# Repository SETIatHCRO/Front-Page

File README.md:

# ata_docs
Documentation related to the Allen Telescope Array at the Hat Creek Radio Observatory in Hat Creek, California

Contents:

[**Analog-Signal-Components:**](Analog-Signal-Components) Documents relating to analog signal components

*Librarian: Alexander Pollak*

[**Antenna:**](Antenna) Documents relating to Antenna geometry and optical design

*Librarian: Alexander Pollak*

[**Antonio-Feed:**](Antonio-Feed) Documents related to V2 Antonio Feeds

*Librarian: Alexander Pollak*

[**Beamformer:**](Beamformer) Documents related to the first ATA beamformer

*Librarian: Billy Barott*

[**EMI:**](EMI) Documents related to site and device electromagnetic interference (EMI/RFI)

*Librarian: Janusz Kulpa*

[**HCRO-Network-Infrastructure:**](HCRO-Network-Infrastructure) Documents and drawings related to the HCRO ethernet infrastructure 

*Librarian: Alexander Pollak*

[**HCRO-Time-Standard:**](HCRO-Time-Standard) Documents and drawings related to the 1pps and 10MHz time distribution.

*Librarian: Alexander Pollak*

[**HVAC-Signal-Processing-Room:**](HVAC-Signal-Processing-Room) Documents and drawings related to the HVAC upgrade.

*Librarian: Alexander Pollak*

[**SITE:**](SITE) Documents related to the HCRO Site

*Librarian: Jon Richards*

[**SonATA:**](SonATA) Documents related to the SETI on ATA (SonATA) System

*Librarian: Jon Richards*

[**NOTES:**](NOTES) The NOTES stored on tumulus. General operating procedures.

*Librarian: Jon Richards*

[**Network:**](Network) Documents and drawings related to network and computer access..

*Librarian: Jon Richards*

Go to the [-> head over to wiki](https://github.com/SETIatHCRO/ata_docs/wiki)

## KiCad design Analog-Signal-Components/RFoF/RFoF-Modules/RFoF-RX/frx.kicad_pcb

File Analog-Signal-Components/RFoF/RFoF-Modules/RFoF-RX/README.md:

# DSA2000 Fiber Receiver

This repository contains the hardware design for the RF over fiber receiver module.
This module provides the data center-local analog signal processing following the conversion of optical to RF with a photodiode.
It is designed to interface with the "Radio Camera Frontend" card, and hence uses board-to-board connectors for the digital control and RF output.
Additionally, this module provides several monitor and control points that will eventually be integrated into the telescope's global monitor and control system.

## Hardware

Designed using KiCad 9, and requires setup of our [library](https://gitlab.com/dsa-2000/asp/kicad-library).

### Artifacts

As part of the CI/CD pipeline for this project, schematics, board files, BoMs, etc. are rendered on each change.
You can find the latest artifacts [here](https://gitlab.com/dsa-2000/asp/rfof/frx/-/jobs/artifacts/main/browse?job=artifacts)

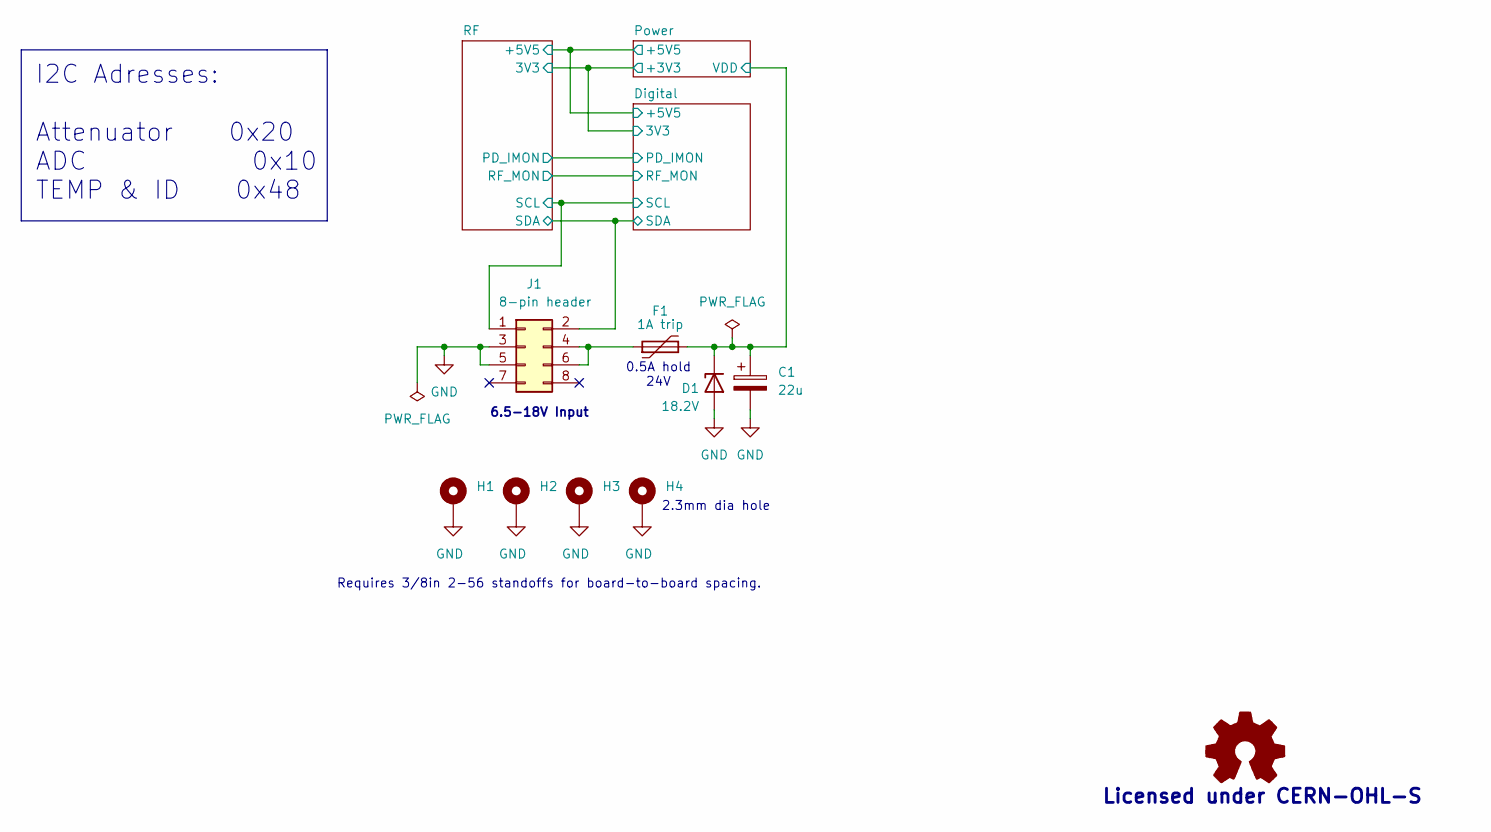
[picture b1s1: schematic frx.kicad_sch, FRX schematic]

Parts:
C1: 22u; CP_EIA-6032-28_Kemet-C; MPN 293D226X9025C2TE3
D1: 18.2V; D_SMA; MPN SMAJ11A
F1: 1A trip; Fuse_1206_3216Metric; MPN 1206L050/24WR
H1, H2, H3, H4: MountingHole_Pad; MountingHole_2_Pad_Via
J1: 8-pin header; HeaderThru8p; MPN 9-146261-0-04

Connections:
/Digital/SCL: J1.1; also elsewhere on the board
/Digital/SDA: J1.2; also elsewhere on the board
/Power/VDD: C1.1, D1.1 (K), F1.2; also elsewhere on the board
GND: C1.2, D1.2 (A), H1.1, H2.1, H3.1, H4.1, J1.3, J1.5; also elsewhere on the board
unnamed: F1.1, J1.4, J1.6

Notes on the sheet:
Requires 3/8in 2-56 standoffs for board-to-board spacing.
6.5-18V Input
Licensed under CERN-OHL-S
2.3mm dia hole
0.5A hold 24V
I2C Adresses: Attenuator 0x20 ADC 0x10 TEMP & ID 0x48

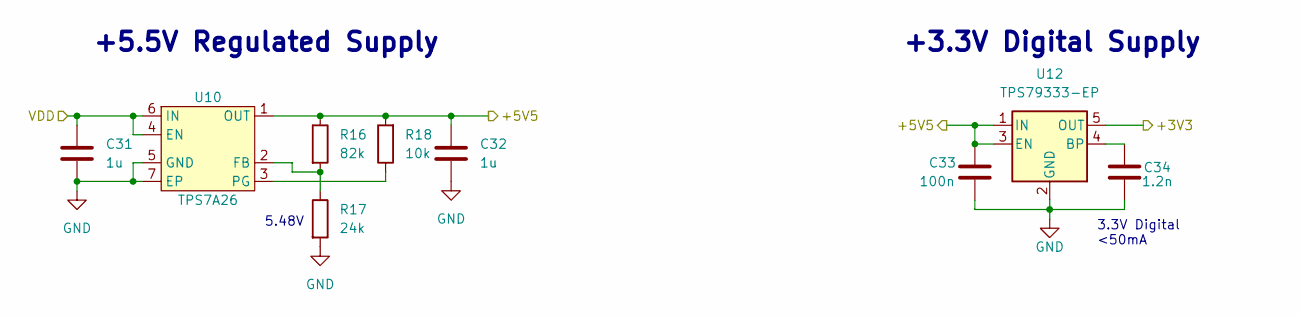
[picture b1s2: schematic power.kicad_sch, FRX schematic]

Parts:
C31, C32: 1u; C_0603_1608Metric; MPN CL10A105KA8NNNC
C33: 100n; C_0402_1005Metric; MPN CL05B104KP5NNNC
C34: 1.2n; C_0603_1608Metric; MPN GCM1885C1H122JA16D
R16: 82k; R_0402_1005Metric; MPN RC0402FR-0782KL
R17: 24k; R_0402_1005Metric; MPN RC0402FR-0724KL
R18: 10k; R_0402_1005Metric; MPN RC0402FR-0710KL
U10: TPS7A26; WSON-6-1EP_2x2mm_P0.65mm_EP1x1.6mm; MPN TPS7A2601DRVR
U12: TPS79333-EP; SOT-23-5; MPN TPS79333DBVR

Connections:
/Digital/3V3: U12.5 (OUT); also elsewhere on the board
/Digital/+5V5: C32.1, C33.1, R16.1, R18.2, U10.1 (OUT), U12.1 (IN), U12.3 (EN); also elsewhere on the board
/Power/VDD: C31.1, U10.4 (EN), U10.6 (IN); also elsewhere on the board
GND: C31.2, C32.2, C33.2, C34.1, R17.2, U10.5 (GND), U10.7 (EP), U12.2 (GND); also elsewhere on the board
unnamed: R16.2, R17.1, U10.2 (FB)
unnamed: R18.1, U10.3 (PG)
unnamed: C34.2, U12.4 (BP)

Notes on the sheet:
+3.3V Digital Supply
3.3V Digital <50mA
5.48V
+5.5V Regulated Supply

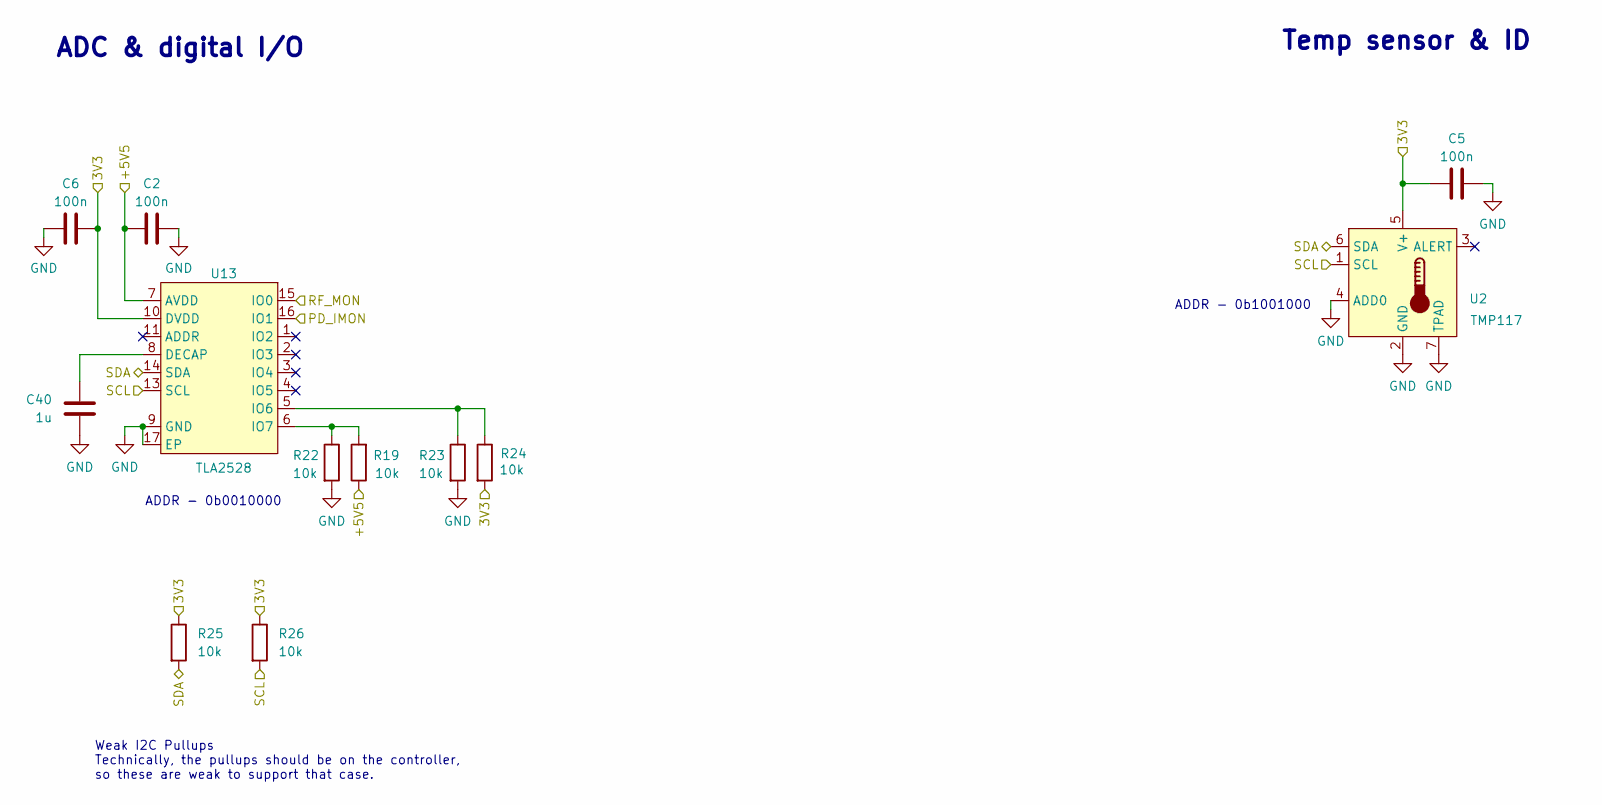
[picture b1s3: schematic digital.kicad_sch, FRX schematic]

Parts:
C2, C5, C6: 100n; C_0402_1005Metric; MPN CL05B104KP5NNNC
C40: 1u; C_0603_1608Metric; MPN CL10A105KA8NNNC
R19, R22, R23, R24, R25, R26: 10k; R_0402_1005Metric; MPN RC0402FR-0710KL
U2: TMP117; WSON-6-1EP_2x2mm_P0.65mm_EP1x1.6mm; MPN TMP117AIDRVR
U13: TLA2528; WQFN-16-1EP_3x3mm_P0.5mm_EP1.68x1.68mm_LargeThermalVias; MPN TLA2528IRTER

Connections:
/Digital/3V3: C5.2, C6.1, R24.2, R25.1, R26.1, U2.5 (V+), U13.10 (DVDD); also elsewhere on the board
/Digital/+5V5: C2.2, R19.1, U13.7 (AVDD); also elsewhere on the board
/Digital/PD_IMON: U13.16 (IO1); also elsewhere on the board
/Digital/RF_MON: U13.15 (IO0); also elsewhere on the board
/Digital/SCL: R26.2, U2.1 (SCL), U13.13 (SCL); also elsewhere on the board
/Digital/SDA: R25.2, U2.6 (SDA), U13.14 (SDA); also elsewhere on the board
GND: C2.1, C5.1, C6.2, C40.1, R22.2, R23.2, U2.2 (GND), U2.4 (ADD0), U2.7 (TPAD), U13.9 (GND), U13.17 (EP); also elsewhere on the board
unnamed: C40.2, U13.8 (DECAP)
unnamed: R23.1, R24.1, U13.5 (IO6)
unnamed: R19.2, R22.1, U13.6 (IO7)

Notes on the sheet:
Temp sensor & ID
ADDR - 0b1001000
ADC & digital I/O
ADDR - 0b0010000
Weak I2C Pullups Technically, the pullups should be on the controller, so these are weak to support that case.

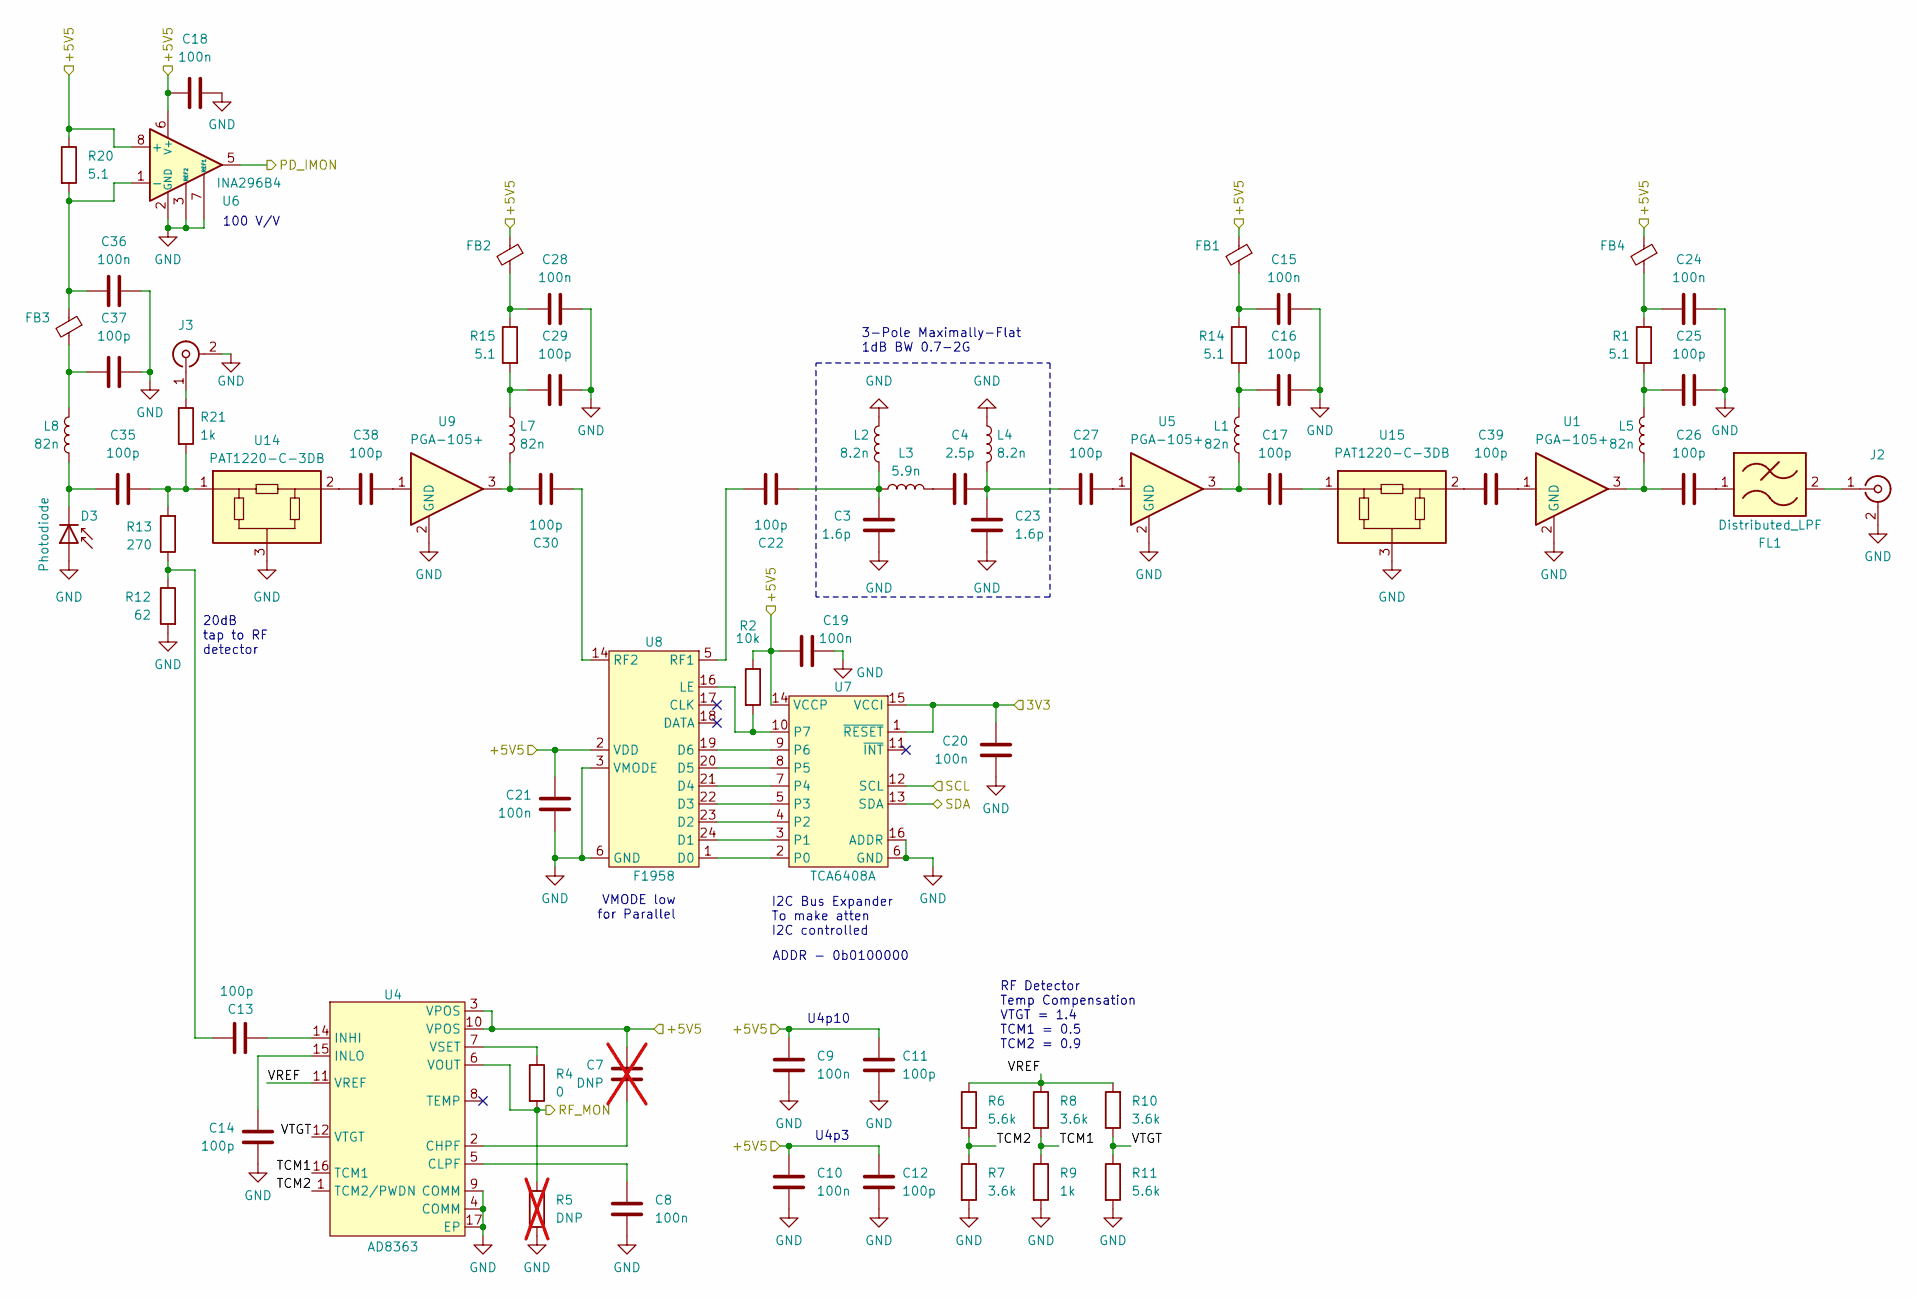
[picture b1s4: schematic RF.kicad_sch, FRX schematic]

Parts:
C3, C23: 1.6p; C_0402_1005Metric; MPN GJM1555C1H1R6WB01D
C4: 2.5p; C_0402_1005Metric; MPN GJM1555C1H2R5WB01D
C7: DNP; C_0402_1005Metric; not fitted
C8, C9, C10, C15, C18, C19, C20, C21, C24, C28, C36: 100n; C_0402_1005Metric; MPN CL05B104KP5NNNC
C11, C12, C13, C14, C16, C17, C22, C25, C26, C27, C29, C30, C35, C37, C38, C39: 100p; C_0402_1005Metric; MPN CBR04C101J3GAC
D3: Photodiode; MountedPD; MPN PPDA-S
FB1, FB2, FB3, FB4: BLM15PG100SN1D; L_0402_1005Metric; MPN BLM15PG100SN1D
FL1: Distributed_LPF; AA_Filter
J2: Conn_Coaxial; SMP_MSLD_PCT_19; MPN SMP_MSLD_PCT_19
J3: Conn_Coaxial; SMP_EdgeMount_PE44482; MPN PE44482
L1, L5, L7, L8: 82n; L_0402_1005Metric; MPN LQW15AN82NG00D
L2, L4: 8.2n; L_0402_1005Metric; MPN LQW15AN8N2G00D
L3: 5.9n; L_0402_1005Metric; MPN LQW15AN5N9B80D
R1, R20: 5.1; R_0402_1005Metric; MPN RC0402FR-075R1L
R2: 10k; R_0402_1005Metric; MPN RC0402FR-0710KL
R4: 0; R_0402_1005Metric; MPN RC0402FR-070RL
R5: DNP; R_0402_1005Metric; not fitted
R6, R11: 5.6k; R_0402_1005Metric; MPN RC0402FR-075K6L
R7, R8, R10: 3.6k; R_0402_1005Metric; MPN RC0402FR-073K6L
R9, R21: 1k; R_0402_1005Metric; MPN RC0402FR-071KL
R12: 62; R_0402_1005Metric; MPN RC0402FR-0762RL
R13: 270; R_0402_1005Metric; MPN RC0402FR-07270RL
R14, R15: 5.1; R_0402_1005Metric; MPN ERJ-2GEJ5R1X
U1, U5, U9: PGA-105+; SOT89-HighTemp; MPN PGA-105+
U4: AD8363; Analog_LFCSP-16-1EP_4x4mm_P0.65mm_EP2.35x2.35mm_ThermalVias; MPN AD8363ACPZ-R7
U6: INA296B4; SOT-23-8; MPN INA296B4IDDFR
U7: TCA6408A; QFN-16-1EP_3x3mm_P0.5mm_EP1.45x1.45mm; MPN TCA6408ARGTR
U8: F1958; TQFN-24-1EP_4x4mm_P0.5mm_EP2.6x2.6mm_ThermalVias; MPN F1958NBGK
U14, U15: PAT1220-C-3DB; RF_Attenuator_Susumu_PAT1220; MPN PAT1220-C-3DB-T5

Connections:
/Digital/3V3: C20.1, U7.1 (~RESET), U7.15 (VCCI); also elsewhere on the board
/Digital/+5V5: C7.1, C9.1, C10.1, C11.2, C12.2, C18.2, C19.1, C21.1, FB1.1, FB2.1, FB4.1, R2.1, R20.1, U4.3 (VPOS), U4.10 (VPOS), U6.6 (V+), U6.8 (+), U7.14 (VCCP), U8.2 (VDD); also elsewhere on the board
/Digital/PD_IMON: U6.5; also elsewhere on the board
/Digital/RF_MON: R4.2, R5.1, U4.6 (VOUT); also elsewhere on the board
/Digital/SCL: U7.12 (SCL); also elsewhere on the board
/Digital/SDA: U7.13 (SDA); also elsewhere on the board
/RF/TCM1: R8.2, R9.1, U4.16 (TCM1)
/RF/TCM2: R6.2, R7.1, U4.1 (TCM2/PWDN)
/RF/VREF: R6.1, R8.1, R10.2, U4.11 (VREF)
/RF/VTGT: R10.1, R11.1, U4.12 (VTGT)
GND: C3.2, C8.2, C9.2, C10.2, C11.1, C12.1, C14.1, C15.2, C16.2, C18.1, C19.2, C20.2, C21.2, C23.2, C24.2, C25.2, C28.2, C29.2, C36.2, C37.2, D3.2 (A), J2.2 (Ext), J3.2 (Ext), L2.1, L4.1, R5.2, R7.2, R9.2, R11.2, R12.2, U1.2 (GND), U4.4 (COMM), U4.9 (COMM), U4.17 (EP), U5.2 (GND), U6.2 (GND), U6.3 (REF2), U6.4 (GND), U6.7 (REF1), U7.6 (GND), U7.16 (ADDR), U7.17 (GND), U8.3 (VMODE), U8.4 (GND), U8.6 (GND), U8.7 (GND), U8.8 (GND), U8.9 (GND), U8.10 (GND), U8.11 (GND), U8.12 (GND), U8.13 (GND), U8.15 (GND), U8.25 (GND), U9.2 (GND), U14.3, U15.3; also elsewhere on the board
unnamed: C4.1, L3.2
unnamed: C13.2, R12.1, R13.1
unnamed: C15.1, FB1.2, R14.1
unnamed: C16.1, L1.1, R14.2
unnamed: C17.1, L1.2, U5.3
unnamed: C17.2, U15.1
unnamed: C3.1, C22.2, L2.2, L3.1
unnamed: C4.2, C23.1, C27.1, L4.2
unnamed: C24.1, FB4.2, R1.1
unnamed: C25.1, L5.1, R1.2
unnamed: C26.1, L5.2, U1.3
unnamed: C26.2, FL1.1
unnamed: C27.2, U5.1
unnamed: C28.1, FB2.2, R15.1
unnamed: C29.1, L7.1, R15.2
unnamed: C30.1, L7.2, U9.3
unnamed: C35.2, R13.2, R21.2, U14.1
unnamed: C37.1, FB3.2, L8.1
unnamed: C38.1, U14.2
unnamed: C38.2, U9.1
unnamed: C39.1, U15.2
unnamed: C39.2, U1.1
unnamed: C35.1, D3.1 (K), L8.2
unnamed: FL1.2, J2.1 (In)
unnamed: J3.1 (In), R21.1
unnamed: C7.2, U4.2 (CHPF)
unnamed: C8.1, U4.5 (CLPF)
unnamed: C13.1, U4.14 (INHI)
unnamed: C14.2, U4.15 (INLO)
unnamed: R4.1, U4.7 (VSET)
unnamed: C36.1, FB3.1, R20.2, U6.1 (-)
unnamed: U7.2 (P0), U8.1 (D0)
unnamed: U7.3 (P1), U8.24 (D1)
unnamed: U7.4 (P2), U8.23 (D2)
unnamed: U7.5 (P3), U8.22 (D3)
unnamed: U7.7 (P4), U8.21 (D4)
unnamed: U7.8 (P5), U8.20 (D5)
unnamed: U7.9 (P6), U8.19 (D6)
unnamed: R2.2, U7.10 (P7), U8.16 (LE)
unnamed: C22.1, U8.5 (RF1)
unnamed: C30.2, U8.14 (RF2)

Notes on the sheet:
U4p3
20dB tap to RF detector
I2C Bus Expander To make atten I2C controlled
100 V/V
ADDR - 0b0100000
U4p10
RF Detector Temp Compensation VTGT = 1.4 TCM1 = 0.5 TCM2 = 0.9
VMODE low for Parallel
3-Pole Maximally-Flat 1dB BW 0.7-2G

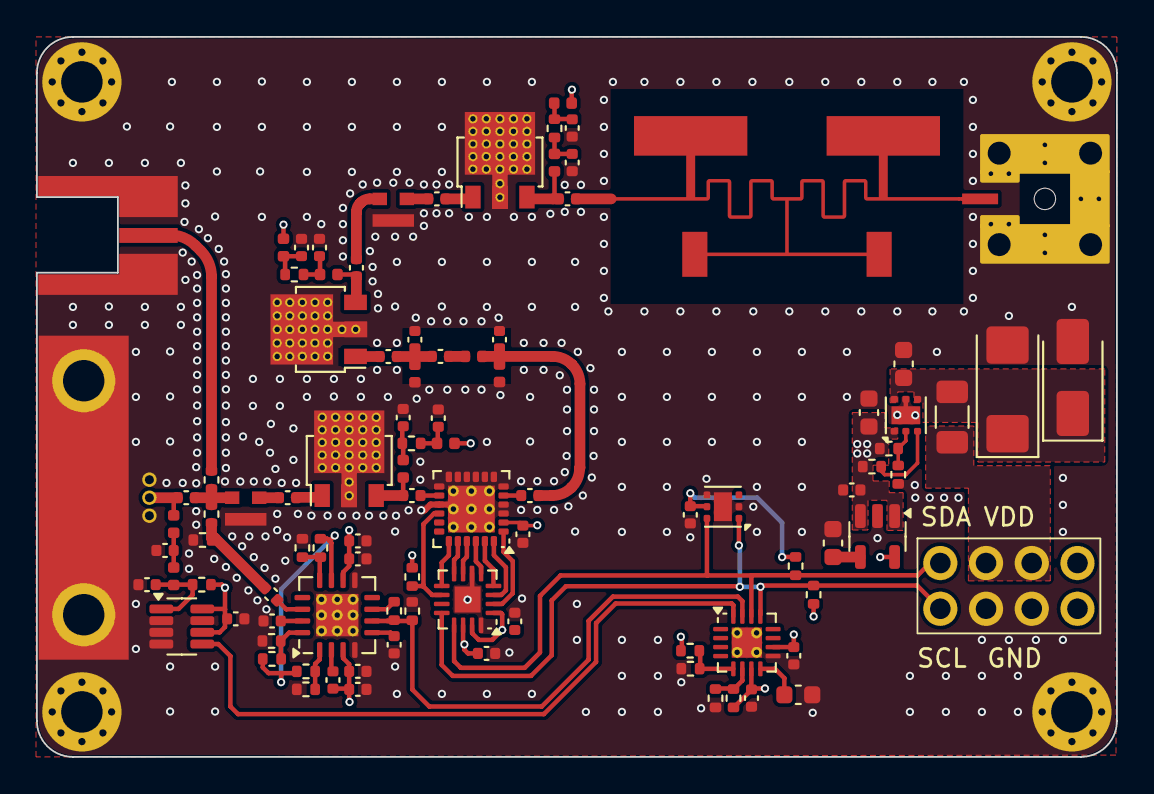
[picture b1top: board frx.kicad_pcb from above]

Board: 4 copper layers, 60.0 x 40.0 mm, 100 parts (0 on the bottom side), 60 nets.

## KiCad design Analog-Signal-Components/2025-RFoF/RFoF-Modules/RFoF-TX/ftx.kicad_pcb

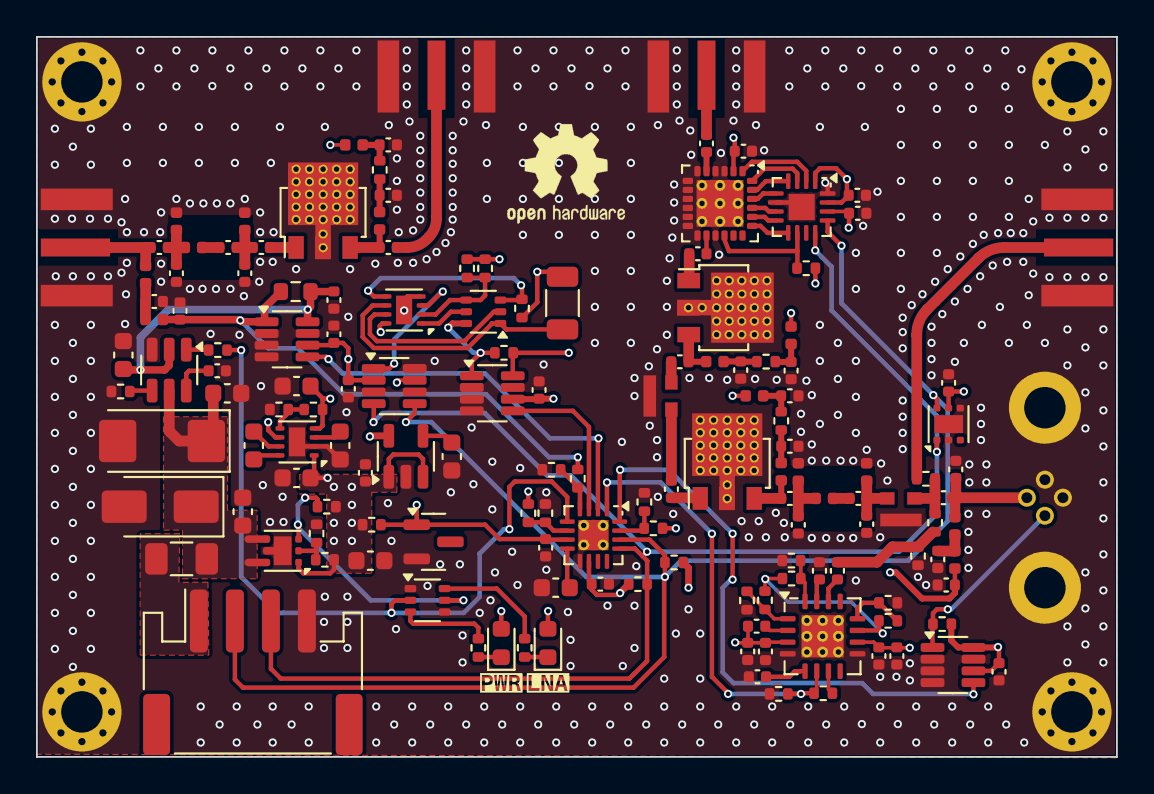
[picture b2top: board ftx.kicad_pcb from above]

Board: 4 copper layers, 60.0 x 40.0 mm, 152 parts (0 on the bottom side), 91 nets.

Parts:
C1: 22u; CP_EIA-6032-28_Kemet-C
C2, C6, C10, C11, C13, C16, C20, C23, C24, C26, C27, C29, C30, C32, C34, C40, C41, C43, C44, C46, C51: 100n; C_0402_1005Metric
C3, C4, C5, C7, C8, C9, C12, C14, C15, C17, C22, C45, C48, C49, C52, C53, C54: 100p; C_0402_1005Metric
C18, C21: DNP; C_0402_1005Metric
C19: 1000p; C_0402_1005Metric
C25: 10u; C_0603_1608Metric
C28, C31, C33, C35, C37: 1u; C_0603_1608Metric
C36, C38: 4.7u; C_0603_1608Metric
C39: 2.2u; C_0603_1608Metric
C42: 1.2n; C_0603_1608Metric
C62, C64, C72, C74: 1.6p; C_0402_1005Metric
C63, C73: 2.5p; C_0402_1005Metric
D2: 18.2V; D_SMA
D3, D4: LED; LED_0603_1608Metric
F1: 1A trip; Fuse_1206_3216Metric
FB1, FB2, FB3, FB4, FB5: BLM15PG100SN1D; L_0402_1005Metric
H1, H2, H3, H4: MountingHole_Pad; MountingHole_2_Pad_Via
J1: 4-pin header; JST_PH_S4B-PH-SM4-TB_1x04-1MP_P2.00mm_Horizontal
J2, J3, J4, J5: Conn_Coaxial; SMA_4Layer
L1, L2, L3, L4, L8: 82n; L_0402_1005Metric
L62, L64, L72, L74: 8.2n; L_0402_1005Metric
L63, L73: 5.9n; L_0402_1005Metric
LD1: LaserDiodeWithBlock
Q1: 2N7002; SOT-363_SC-70-6
Q3: BC846; SOT-363_SC-70-6
R1, R12, R15, R16, R17, R23, R24, R30, R31, R35, R36, R41: 10k; R_0402_1005Metric
R2: 0; R_0402_1005Metric
R3: 3.32k; R_0402_1005Metric
R4: 100; R_0402_1005Metric
R5, R9: 5.6k; R_0402_1005Metric
R6, R8, R11, R13, R39: 1k; R_0402_1005Metric
R7, R32: 270; R_0402_1005Metric
R10, R37, R38: 3.6k; R_0402_1005Metric
R19: 11k; R_0402_1005Metric
R20: 0.5; R_0603_1608Metric
R21: 620k; R_0402_1005Metric
R22: 200k; R_0402_1005Metric
R25: 62; R_0402_1005Metric
R26, R27, R51: 5.1; R_0402_1005Metric
R28: 20, 1/4W; R_1206_3216Metric
R29: 1; R_0402_1005Metric
R33: 82k; R_0402_1005Metric
R34: 24k; R_0402_1005Metric
R40: DNP; R_0402_1005Metric
U2, U6, U10: PGA-105+; SOT89-HighTemp
U3: TCA6408A; QFN-16-1EP_3x3mm_P0.5mm_EP1.45x1.45mm
U4: CAT5171; SOT-23-8
U5: F1958; TQFN-24-1EP_4x4mm_P0.5mm_EP2.6x2.6mm_ThermalVias
U7, U11, U17: INA296B4; SOT-23-8
U8: AD8363; Analog_LFCSP-16-1EP_4x4mm_P0.65mm_EP2.35x2.35mm_ThermalVias
U9: TLV9102; WSON-8-1EP_2x2mm_P0.5mm_EP0.9x1.6mm
U12: TLA2528; WQFN-16-1EP_3x3mm_P0.5mm_EP1.68x1.68mm_LargeThermalVias
U13: TMP117; WSON-6-1EP_2x2mm_P0.65mm_EP1x1.6mm
U15: MP5035; TSOT-23-6
U16: TPS7A26; WSON-6-1EP_2x2mm_P0.65mm_EP1x1.6mm
U18: LM27761; WSON-8-1EP_2x2mm_P0.5mm_EP0.9x1.6mm
U19: TPS79333-EP; SOT-23-5
U20: LM4040-5.0; SOT-23
U21, U22: PAT1220-C-3DB; RF_Attenuator_Susumu_PAT1220
kibuzzard-65317E70: G***; kibuzzard-65317E70
kibuzzard-65317EA1: G***; kibuzzard-65317EA1

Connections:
/Digital/3V3: C27.2, C30.2, C44.1, R15.2, R16.2, R31.2, U3.1 (~RESET), U3.15 (VCCI), U12.10 (DVDD), U13.5 (V+), U19.5 (OUT)
/Digital/+5V5: C10.1, C11.1, C13.2, C17.2, C18.1, C20.1, C24.1, C26.2, C35.1, C36.1, C40.1, C41.2, C45.2, C46.1, D3.2 (A), D4.2 (A), FB2.1, FB3.1, FB5.1, R4.1, R12.1, R24.2, R32.1, R33.1, R35.2, U3.14 (VCCP), U4.2 (VDD), U5.2 (VDD), U7.6 (V+), U7.8 (+), U8.3 (VPOS), U8.10 (VPOS), U9.8 (V+), U11.6 (V+), U16.1 (OUT), U17.6 (V+), U18.1 (VIN), U18.6 (EN), U19.1 (IN), U19.3 (EN)
/Digital/+5_VREF: C29.2, R1.1, R23.1, R32.2, U4.7 (B), U12.7 (AVDD), U20.1 (K)
/Digital/LD_IMON: U12.3 (IO4), U17.5
/Digital/LNA_EN: Q1.2 (G), R17.2, U12.5 (IO6)
/Digital/LNA_IMON: U11.5, U12.2 (IO3)
/Digital/PD_IMON: U7.5, U12.16 (IO1)
/Digital/RF_MON: R2.2, R40.1, U8.6 (VOUT), U12.1 (IO2)
/Digital/SCL: J1.3, R16.1, U3.12 (SCL), U4.4 (SCL), U12.13 (SCL), U13.1 (SCL)
/Digital/SDA: J1.2, R15.1, U3.13 (SDA), U4.5 (SDA), U12.14 (SDA), U13.6 (SDA)
/Digital/VLNA: C2.1, FB1.1, R20.1, R41.2, U11.1 (-)
/Power/-5V: C39.1, R11.2, R21.1, R28.2, U9.4 (V-), U9.9 (PAD), U18.4 (VOUT)
/Power/VDD: C1.1, C31.2, C33.1, D2.1 (K), F1.2, U15.5 (VIN), U16.4 (EN), U16.6 (IN)
/RF2/TCM1: R8.1, R37.2, U8.16 (TCM1)
/RF2/TCM2: R9.2, R10.1, U8.1 (TCM2/PWDN)
/RF2/VREF: R9.1, R37.1, R38.2, U8.11 (VREF)
/RF2/VTGT: R5.1, R38.1, U8.12 (VTGT)
GND: C1.2, C2.2, C3.2, C6.2, C7.2, C10.2, C11.2, C13.1, C14.2, C16.2, C17.1, C20.2, C21.2, C22.2, C23.2, C24.2, C25.1, C26.1, C27.1, C28.2, C29.1, C30.1, C31.1, C32.2, C33.2, C34.1, C35.2, C36.2, C38.2, C39.2, C40.2, C41.1, C42.1, C43.2, C44.2, C45.1, C46.2, C48.1, C51.2, C52.2, C62.2, C64.2, C72.2, C74.2, D2.2 (A), H1.1, H2.1, H3.1, H4.1, J1.4, J2.2 (Ext), J3.2 (Ext), J4.2 (Ext), J5.2 (Ext), L62.1, L64.1, L72.1, L74.1, LD1.1, LD1.3, Q1.1 (S), Q1.4 (S), R3.1, R5.2, R8.2, R10.2, R19.2, R22.2, R25.2, R30.2, R34.2, R36.1, R40.2, U2.2 (GND), U3.6 (GND), U3.16 (ADDR), U3.17 (GND), U4.3 (GND), U4.6 (AD0), U4.8 (A), U5.3 (VMODE), U5.4 (GND), U5.6 (GND), U5.7 (GND), U5.8 (GND), U5.9 (GND), U5.10 (GND), U5.11 (GND), U5.12 (GND), U5.13 (GND), U5.15 (GND), U5.25 (GND), U6.2 (GND), U7.2 (GND), U7.3 (REF2), U7.4 (GND), U7.7 (REF1), U8.4 (COMM), U8.9 (COMM), U8.17 (EP), U10.2 (GND), U11.2 (GND), U11.3 (REF2), U11.4 (GND), U11.7 (REF1), U12.9 (GND), U12.17 (EP), U13.2 (GND), U13.4 (ADD0), U13.7 (TPAD), U15.3 (GND), U16.5 (GND), U16.7 (EP), U17.2 (GND), U17.3 (REF2), U17.4 (GND), U17.7 (REF1), U18.2 (GND), U18.9 (PAD), U19.2 (GND), U20.2 (A), U21.3, U22.3
unnamed: C3.1, FB1.2, L1.1
unnamed: C4.2, C62.1, L62.2, L63.1
unnamed: C5.1, C63.2, C64.1, L64.2
unnamed: C5.2, U2.1
unnamed: C6.1, FB2.2, R27.1
unnamed: C7.1, L2.1, R27.2
unnamed: C8.1, L2.2, U2.3
unnamed: C12.2, U10.1
unnamed: C14.1, L3.1, R26.2
unnamed: C15.1, L3.2, U6.3
unnamed: C15.2, C72.1, L72.2, L73.1
unnamed: C19.1, C21.1, L4.1, LD1.2
unnamed: C19.2, R6.2, R7.2, U22.2
unnamed: C22.1, FB4.1, L4.2
unnamed: C43.1, FB3.2, R26.1
unnamed: C49.1, R7.1, R25.1
unnamed: C51.1, FB5.2, R51.1
unnamed: C52.1, L8.1, R51.2
unnamed: C53.1, L8.2, U10.3
unnamed: C53.2, U21.1
unnamed: C54.1, U21.2
unnamed: C54.2, U6.1
unnamed: C63.1, L63.2
unnamed: C73.1, L73.2
unnamed: C73.2, C74.1, L74.2, U22.1
unnamed: D3.1 (K), R39.1
unnamed: D4.1 (K), R13.1
unnamed: F1.1, J1.1
unnamed: C4.1, J2.1 (In), L1.2
unnamed: C8.2, J3.1 (In)
unnamed: C9.1, J4.1 (In)
unnamed: J5.1 (In), R6.1
unnamed: Q1.6 (D), R13.2
unnamed: Q1.3 (D), R39.2
unnamed: Q1.5 (G), R35.1, U16.3 (PG)
unnamed: Q3.2 (B1), U9.7
unnamed: Q3.6 (C1), R29.1, U17.1 (-)
unnamed: Q3.1 (E1), R28.1, U9.6 (-)
unnamed: Q3.5 (B2), U9.1
unnamed: Q3.3 (C2), R11.1, U9.5 (+)
unnamed: Q3.4 (E2), R1.2, R23.2, U9.2 (-)
unnamed: U3.2 (P0), U5.1 (D0)
unnamed: U3.3 (P1), U5.24 (D1)
unnamed: U3.4 (P2), U5.23 (D2)
unnamed: U3.5 (P3), U5.22 (D3)
unnamed: U3.7 (P4), U5.21 (D4)
unnamed: U3.8 (P5), U5.20 (D5)
unnamed: U3.9 (P6), U5.19 (D6)
unnamed: R12.2, U3.10 (P7), U5.16 (LE)
unnamed: U4.1 (W), U9.3 (+)
unnamed: C9.2, U5.5 (RF1)
unnamed: C12.1, U5.14 (RF2)
unnamed: LD1.4, R4.2, U7.1 (-)
unnamed: C18.2, U8.2 (CHPF)
unnamed: C16.1, U8.5 (CLPF)
unnamed: C49.2, U8.14 (INHI)
unnamed: C48.2, U8.15 (INLO)
unnamed: R2.1, U8.7 (VSET)
unnamed: C25.2, C34.2, R20.2, U11.8 (+), U15.2 (SOURCE)
unnamed: C28.1, U12.8 (DECAP)
unnamed: R24.1, R30.1, U12.15 (IO0)
unnamed: R3.2, R41.1, U12.4 (IO5)
unnamed: R31.1, R36.2, U12.6 (IO7)
unnamed: C32.1, U15.6 (DV/DT)
unnamed: R17.1, U15.1 (EN)
unnamed: R19.1, U15.4 (ILIMIT)
unnamed: R33.2, R34.1, U16.2 (FB)
unnamed: C23.1, FB4.2, R29.2, U17.8 (+)
unnamed: C37.1, U18.8 (C+)
unnamed: C37.2, U18.7 (C-)
unnamed: C38.1, U18.3 (CPOUT)
unnamed: R21.2, R22.1, U18.5 (VFB)
unnamed: C42.2, U19.4 (BP)

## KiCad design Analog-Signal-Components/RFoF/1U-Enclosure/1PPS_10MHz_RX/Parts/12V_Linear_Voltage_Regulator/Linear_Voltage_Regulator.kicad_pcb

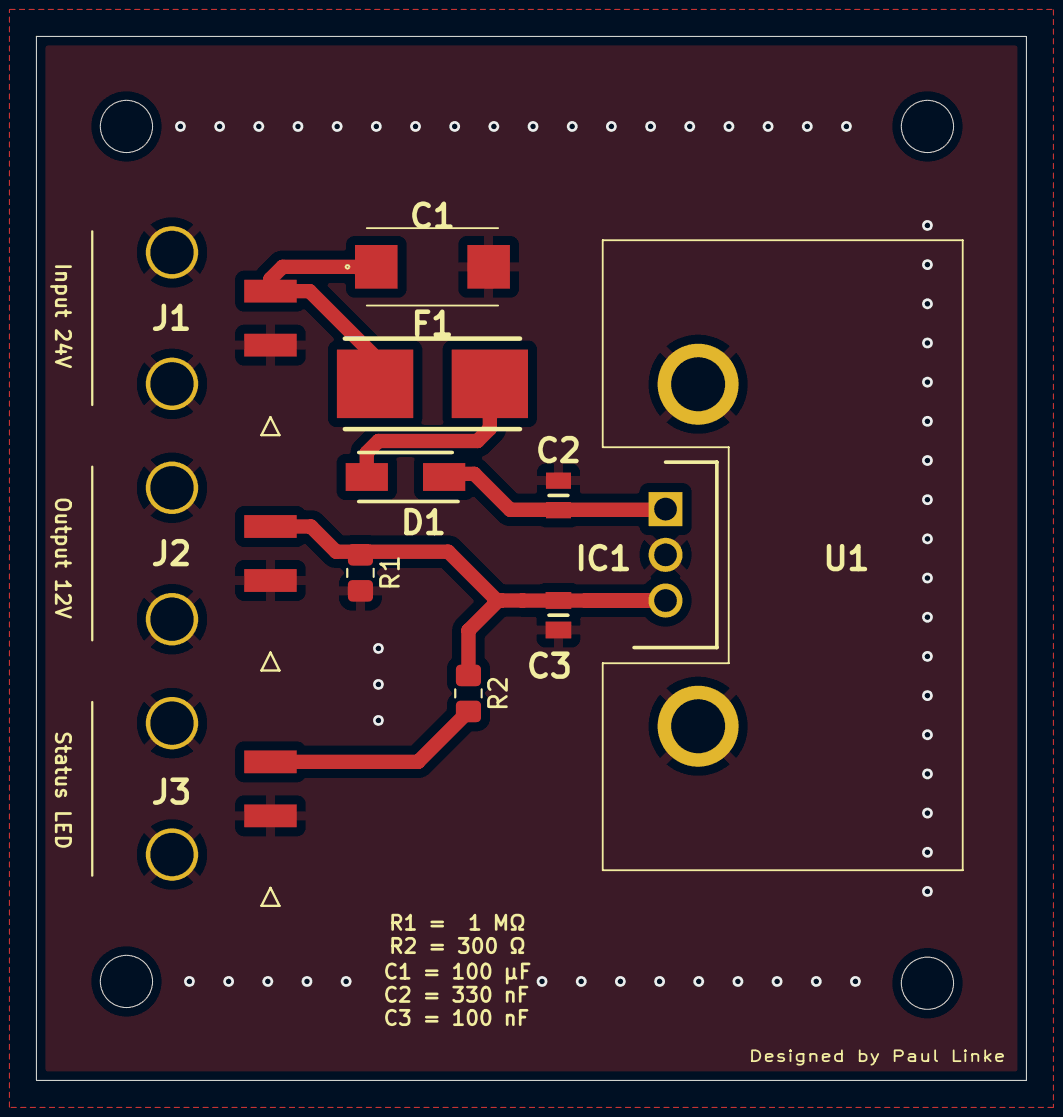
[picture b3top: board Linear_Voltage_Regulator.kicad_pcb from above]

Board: 2 copper layers, 55.0 x 58.0 mm, 12 parts (0 on the bottom side), 6 nets.

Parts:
C1: 100 uF; T491X
C2: 330 nF; CAPC2012X100N
C3: 100 nF; CAPC2012X140N
D1: S1M; DIOM5227X270N
F1: 0154001.DRT
IC1: LDO; TO254P460X1010X1720-3P
J1: Input 12V; 43650-02YY_091011
J2: Output 6V; 43650-02YY_091011
J3: Status LED; 43650-02YY_091011
R1: 1 MOhm; R_0805_2012Metric_Pad1.20x1.40mm_HandSolder
R2: 500 Ohm; R_0805_2012Metric_Pad1.20x1.40mm_HandSolder
U1: Heatsink; 513002B02500G

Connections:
GND: C1.2, C2.2, C3.2, IC1.2 (COMMON), J1.1, J1.3, J1.4, J2.1, J2.3, J2.4, J3.1, J3.3, J3.4, R1.2, U1.1, U1.2
unnamed: C1.1, F1.1, J1.2
unnamed: D1.2, F1.2
unnamed: C2.1, D1.1, IC1.1 (INPUT)
unnamed: C3.1, IC1.3 (OUTPUT), J2.2, R1.1, R2.1
unnamed: J3.2, R2.2

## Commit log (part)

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2021-11-10 Add meeting slides
2021-11-18 added attemplifier memo
2021-11-19 Add November 18 slides
2021-11-19 Create new directory for Jack's slides
2021-11-19 Upload Jack's delay tracking tests
2021-11-19 added meeting slide
2022-01-12 Adding ATA operations brainstorming documents
2022-01-12 Created "Operations" folder
2022-01-12 Deleted Operations file to move to correct folder
2022-01-12 Deleted init.txt
2022-01-12 Added row to project list
2022-01-14 Added README
2022-01-14 Deleted Excel file in transfer to Google Sheets
2022-01-14 added meeting presentation
2022-01-27 added GRASP Memo
2022-01-28 Added first draft of RFI Survey Design Memo
2022-01-28 Messed up path (again)
2022-01-28 Create proxy.txt to make a new folder
2022-02-20 added 4e measurement
2022-02-20 added metadata
2022-02-21 added direct feed measurement with SA
2022-02-24 Guide to Observe with the ATA
2022-02-24 Observation Guide
2022-02-24 Calibrating with ATA RFSoc correlator
2022-02-24 Upload Realtime Correlator
2022-02-24 Upload Realtime correlator calibration document
2022-02-26 Upload Calibration Document
2022-03-08 Minor wire harness updates
2022-03-09 Add processing backend information
2022-03-09 added meeting slides
2022-03-15 Attempifier Module fixes
2022-03-23 added LO firmware files
2022-03-25 Added slides from 02/2022-03/2022
2022-03-28 updated Tsys data
2022-03-28 Update README.md
    First go at readme.md
2022-03-28 Add moon tsys measurements
2022-03-31 added files
2022-04-04 added tip-link documents
2022-04-11 Add redis_6379
    `redis` executer script
2022-04-11 Add redis configuration file
2022-04-11 Add .service file
2022-04-11 Modify redis.service
    Modify redis.service to use /run instead of /var/run
2022-04-11 Modify 6379.conf
    Modify 6379.conf to use /run instead of /var/run
2022-04-11 Update redis_6379
    to use $REDISHOST for shutdown
2022-04-12 measured 3c and 4j
2022-05-03 Add "Terminology" section to the beamforming memo
2022-05-24 Added 03/2022 - 05/2022 slides
2022-06-09 updated feed parts document
2022-06-16 Wiring Updates
2022-06-16 Wiring Update
2022-08-11 PAX box 14 calibrated
2022-09-02 PAX Boxes tested
2022-09-02 Feed Updates
2022-09-02 PAX Box updates
2022-09-08 Wire Harness update
2022-09-14 Adding Liebert AC System temperature warning
2022-09-15 Accel hire harness update
2022-09-15 added manuals
2022-09-15 added Tsys 5e
2022-09-15 wire harness edits
2022-09-16 Add backend antenna swap manual
2022-09-16 Correct directory structure
2022-09-20 Recent PAX box tests
2022-09-21 added Tsys measurements
2022-09-21 added ignore list
2022-09-28 added feed info
2022-09-29 added 48V check column
2022-10-06 updated feeds
2022-10-11 Wire harness updates
2022-10-24 Wire harness tweeks
2022-10-26 Wire Harness COMPLETE
2022-12-05 Add VNC manual
    v1.0
2023-01-19 add NRDZ sub-directory
2023-01-19 add link for tardys4
2023-02-08 added RFSoC document
2023-03-14 added building document
2023-04-14 Added the general specification document
2023-04-14 Created pseudo-unit tests
    Created some assert-statement-style unit tests for the "first step" function that plots the diameter of two different beams, based on the 3.5/f_GHz ATA primary beam width function.
2023-04-24 Uploading Brandon's first pass at the script
    (originally titled "seti1.txt")
2023-04-24 Updated to use astropy (Sofia's edit)
2023-04-24 Use to test beamformer_functions.py
2023-05-08 added building summary
2024-02-01 First log of NRDZ Network Setup and Update
    Details on update to the WR switch and sensor component fixes and deployment.
2024-02-12 added IF mapping
2024-02-12 added old labeling document
2024-02-12 added files for IF Power Splitter
2024-02-12 added BIOS modification Document
2024-02-13 added manual for HighPoint RAID Controller configuration
2024-02-14 Latex template for the IF splitter docs.
2024-02-15 Start of IF splitter document.
2024-02-21 First complete version of the IF Splitter doc.
2024-02-27 Improved version with corrections.
2024-03-04 added manual in MEMOS on how to read raw encoder values
2024-03-05 added feed firmware documentation
2024-03-06 First incomplete draft of the doc for the screen room test measurements.
2024-03-07 Fiday meeting notes (ATA update, Marc)
2024-03-22 Added documentation for elevation encoder cable.
2024-03-28 Thursday meeting slides
2024-03-28 rename meeting notes to match name convention
2024-04-02 Added VNA measurements for first IF splitter
2024-04-03 Python script to generate the LateX text that include all the VNA result plots.
2024-04-04 20240404 meeting slides
2024-04-05 First draft of GReX EMI measurements
2024-04-08 First draft of the GReX spectrum measurements document.
2024-04-08 Added info on peak finder.
2024-04-08 GReX measurment corrections: cable length, VBW RBW units, 30dB and SNAP firmware.
2024-04-08 Minor typo corrections for the GReX document.
2024-04-11 VNA plots added for both IF splitter modules.
2024-04-11 2024 04 11 meeting notes.
2024-04-11 Added PAM new design slides.
2024-04-12 moved backend config into dsp folder
2024-04-17 added Tsys measurements 3c and 5b
2024-04-18 20240418 meeting slides added
2024-04-19 Add phone notes and provisioning scripts.
2024-04-19 More groups, tweak README.md formatting.
2024-04-19 Explain how to add nested groups.
2024-04-23 Phonebook, provisioning tweaks for auto-answer/paging
2024-04-26 Roll out more phones, improve scripts and firmware process.
2024-04-29 Meeting slides added
2024-04-30 Move phone provisioning data to util repo
2024-05-01 added technical details document
2024-05-03 moved HCRO building summary
2024-05-09 Rename meeting note
2024-05-13 added Tsys measurement for antenna 2c
2024-05-13 added low res building summary
2024-05-21 added map of antenna locations
2024-05-21 Correct length to 25ft for tunning C
2024-05-23 Minor corrections
2024-05-24 updated DSP mapping document
2024-05-24 Changed IF cable numbering to reflect actual DSP setup
2024-06-12 Adding IF attenuation values
2024-06-12 Added 0 attenuators
2024-06-20 added tsys measurement for 2a
2024-07-02 added powewr distribution information HCRO
2024-07-27 added concrete pad layout
2024-08-14 added drive amplifier parameters
2024-08-16 added accelnet documentation
2024-08-19 finished drive box acellnet module manual
2024-08-20 added pdf version
2024-11-04 added antenna pcb files
2024-12-02 added RFSoC Network and IP mapping
2024-12-02 Create 2024-10 UVW and beam patterns
2024-12-02 Populate README.md file
2024-12-02 Add scripts to the UVW and beam patterns memo
2024-12-03 Remove autocorrelations from grid
2024-12-06 Update README.md for better UVWs
2024-12-06 Make multi-frequency and modify source
2024-12-11 make uniform grid, and increase freq res
2024-12-11 Update README.md
    To include more plots and their zoomed-in versions
2024-12-11 Update README.md
    not assuming single-frequency anymore
2025-01-09 added PAM box pdf
2025-02-05 added LNF datasheets
2025-02-06 added LNA wiring document
2025-02-24 added QRFH measurement
2025-03-01 added camera building drawing
2025-03-05 push
2025-03-11 updated high point raid and IF tunings
2025-03-20 fixed a layout problem
2025-03-28 removed .DS_Store files
2025-03-28 changed character that are not allowed in windows OS
2025-03-28 removed tailing space on folder names
2025-03-28 deleted old file
2025-03-28 renamed log files
2025-03-28 Added PAM 2025 folder
2025-04-11 updated box design for PAM modules
2025-04-11 added final measurements
2025-06-23 added emergancy maps and change folder layout
2025-06-24 added report
2025-06-24 new folder for RFCB project
2025-06-24 replacement of datasheet
2025-06-24 added old documentation
2025-07-01 added font fro PDF
2025-07-01 added picture of RFCB optic module
2025-07-09 added lna datasheets
2025-07-18 did HC measurement on 5B
2025-07-21 added dormitory overview
2025-07-22 updated rate sheet
2025-07-22 removed old rate sheets
2025-08-05 Add Tape-Configuration.drawio
2025-09-18 Network Wall Port document for Mainlab
2025-09-22 Network Wall Port document updates for EShop
2025-10-09 Moved Wall Port document and renamed.
2025-10-15 added RFoF folder
2025-10-22 added Tsys measurment 2B
2025-10-29 added RFoF rx enclosure
2025-11-12 added alpaca documents
2025-11-12 ALPACA shed cad + document updates
2025-11-14 added power detector assembly
2025-11-15 amplifier-v3 + detector-v2
2025-11-17 Remove duplicate file
2025-11-18 det/amp docs update/gerber
2025-11-18 added connector assembly
2025-11-18 tidy up analog componets
2025-11-19 pam module directories reorganized
2025-11-20 amp & detector BOM, datasheets
2025-11-20 updated documentation
2025-11-21 added instructions for cable assembly for power cord
2025-11-24 Updates to the HighPoint RAID controller notes
2025-12-09 updated detector datasheet
2025-12-09 Add detector module assembly report
2025-12-18 updated bom for rfof enclosure
2025-12-18 RFoF 1pps/10MHz enclosure added
2025-12-18 added datasheet for Bias Tee
2025-12-19 Parts list 1PPS/10MHz enclosure
2026-01-07 Updates to Network-Wall-Port-Mapping.
2026-01-12 BNC -> SMA on RFoF 1PPS front panel
2026-01-12 1PPS enclosure BNC -> SMA, inventor + drawings
2026-01-15 Updated instructions for cryo cooler wire harness
2026-01-15 powerpoint instructions - some images removed due to filesize limitations
2026-01-15 updated feed part inventory
2026-01-16 12V LRV in 1pps RFoF Enc
2026-01-16 Tsys measurement
2026-01-21 1pps front panel led
2026-01-21 1pps fpe
2026-01-22 1pps base plate fpe
2026-01-22 1pps base plate fpe edit
2026-01-23 base plate drawings 1pps
2026-01-24 Power detector buildout, p-v modules 000 and 001
2026-01-26 p-v curve detector module 002
    q
    exit
2026-01-26 filename updates
2026-01-26 LED Converter in RFoF 1U Enc
2026-01-26 preliminary start to s params
2026-01-27 plot_sparams reordering debug
2026-01-28 pv module002 take 2, data
2026-01-28 p-v plot
2026-01-28 1b tsys measurements
2026-01-28 1b tsys, ypol bad, xpol needs redone
2026-01-28 1b Tsys meas 2
2026-01-28 2l Tsys Measurement
2026-01-28 s-param for module 002
2026-01-29 initial S-param measurements in lab for QRFHv3 feed 005 (ant1c)
2026-01-29 updated title and naming convention, qrfh s-params
2026-02-17 New facility planning map.
2026-02-17 Updates to facility emergency planning map
2026-02-19 Spelling corrections to Facility Emergency Planning Map
2026-02-20 RFoF PCB fixes
2026-02-25 LNA cable instructions
2026-02-26 1h hot/cold measurements
2026-03-06 power detector p-v curves
2026-03-07 p-v curves, modules 003 014 015
2026-03-09 pv curves module 017, 019, 021, 024
2026-03-10 p-v curve module 026
2026-03-20 p-v curves modules 027, 041, 055, 082
2026-03-24 folder reorg, detector module reports
2026-03-25 p-v curves and reports modules 033 034 038
2026-03-26 p-v curves and test reports
2026-03-27 test reports and p-v curves
2026-03-31 p-v curves and test reports, 10 modules
2026-04-01 Visitor vidio player instructions.
2026-04-01 p-v curves and test reports, 5 modules
2026-04-02 1k hot/cold measurements after d-pump repair
2026-04-06 Minor Update to Video Player instructions
2026-04-14 more s-parameters and test reports
2026-04-14 file reorg, cleanup, pdf reports
2026-04-17 remaining detector module p-v and s11 data
2026-04-17 p-v plots and s11 plots
    :wq
2026-04-17 PAM-interface
2026-04-17 all modules now have test reports
2026-05-05 added Weather Station settings
2026-05-20 Add Generator Run Log for printing
2026-05-26 Tsys measurements 3c,3d,3l,4j,5b,5e
2026-05-28 Bit pattern report added
2026-06-01 PAM-Interface delay lines added
2026-06-01 PAM-Interface v2
2026-06-01 PAM-Interface v2 BOM
2026-06-02 hot/cold measurements 2a,2b,2h,2l,2m
2026-06-02 hot/cold measurement 1e
2026-06-03 hot/cold measurements 1d,1g,1h,2f,2j,2d,2e
2026-06-03 hot/cold plots 1g
2026-06-15 hot/cold measurement 2e - post filming
2026-06-17 attenuator PAM interface measurements
2026-06-18 PV curves 005,053
2026-06-18 module testing
2026-06-22 Updates for Optics Lab Evacuation Map
2026-06-22 p-v data for more detectors
2026-06-23 p-v data for remaining power detector modules
2026-06-23 last few p-v datasets
2026-06-23 reworked module s-params
2026-06-24 clean atten measurements PAM interface
2026-06-25 additional figures
2026-06-29 4e hot/cold
2026-06-29 filestructure fix
